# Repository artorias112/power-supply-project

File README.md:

# power-supply-project
Simple AC power supply design

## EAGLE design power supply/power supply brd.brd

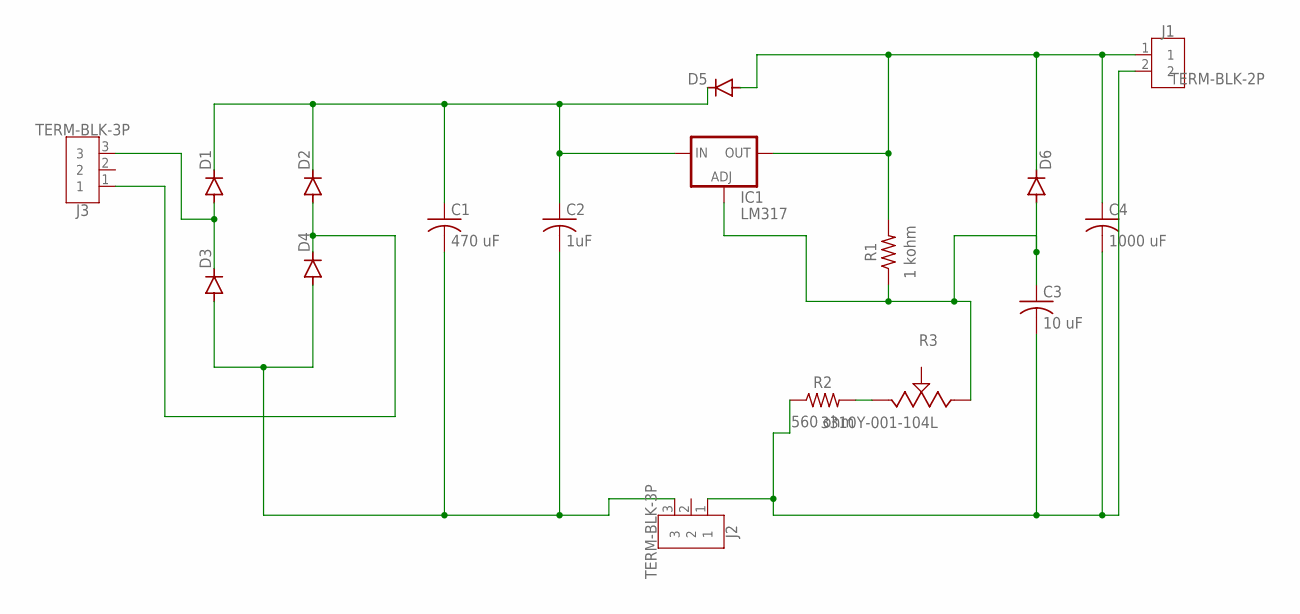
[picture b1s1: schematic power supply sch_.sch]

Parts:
C1: 470 uF; CAPRD550W60D1025H1250B
C2: 1uF; CAPRD550W60D1025H1250B
C3: 10 uF; CAPRD550W60D1025H1250B
C4: 1000 uF; CAPRD550W60D1025H1250B
D1, D2, D3, D4, D5, D6: 1N4004; DO41-10
IC1: LM317; 317TL
J1: TERM-BLK-2P; TERMBLK_508-2N
J2, J3: TERM-BLK-3P; TERMBLK_508-3N
R1: 1 kohm; RESAD724W46L381D178B
R2: 560 ohm; RESAD724W46L381D178B
R3: 3310Y-001-104L; 3310Y-001-104L-ND

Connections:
unnamed: D1.A, D3.C, J3.3
unnamed: C1.1, C2.1, D1.C, D2.C, D5.C, IC1.3 (IN)
unnamed: C1.2, C2.2, D3.A, D4.A, J2.3
unnamed: D2.A, D4.C, J3.1
unnamed: C3.2, C4.2, J1.2, J2.1, R2.1
unnamed: R2.2, R3.1
unnamed: C4.1, D5.A, D6.C, IC1.2 (OUT), J1.1, R1.2
unnamed: C3.1, D6.A, IC1.1 (ADJ), R1.1, R3.3

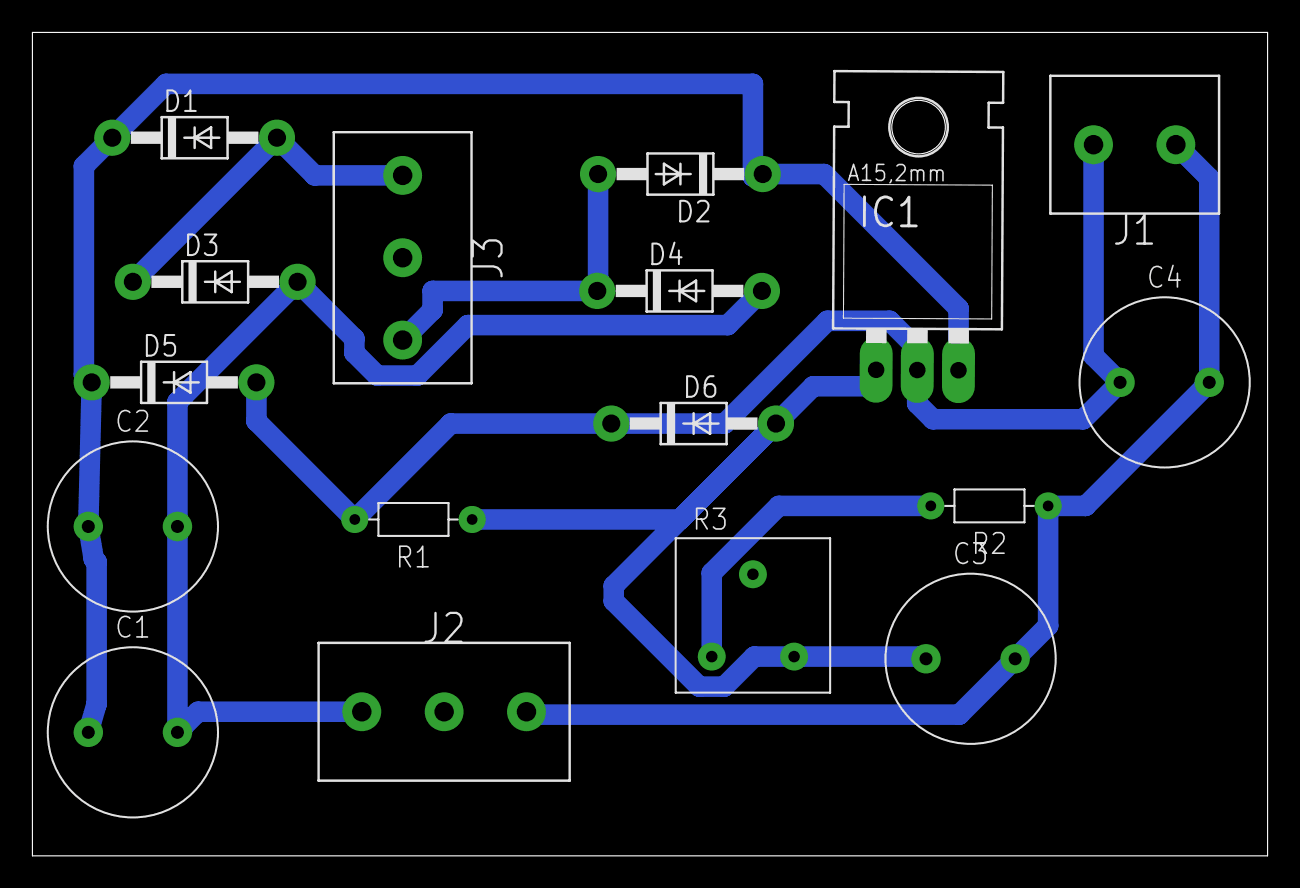
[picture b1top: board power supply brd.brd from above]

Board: 2 copper layers, 76.2 x 50.8 mm, 17 parts (0 on the bottom side), 8 nets.

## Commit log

2024-12-22 Add files via upload
    nitial upload of schematics and design files
